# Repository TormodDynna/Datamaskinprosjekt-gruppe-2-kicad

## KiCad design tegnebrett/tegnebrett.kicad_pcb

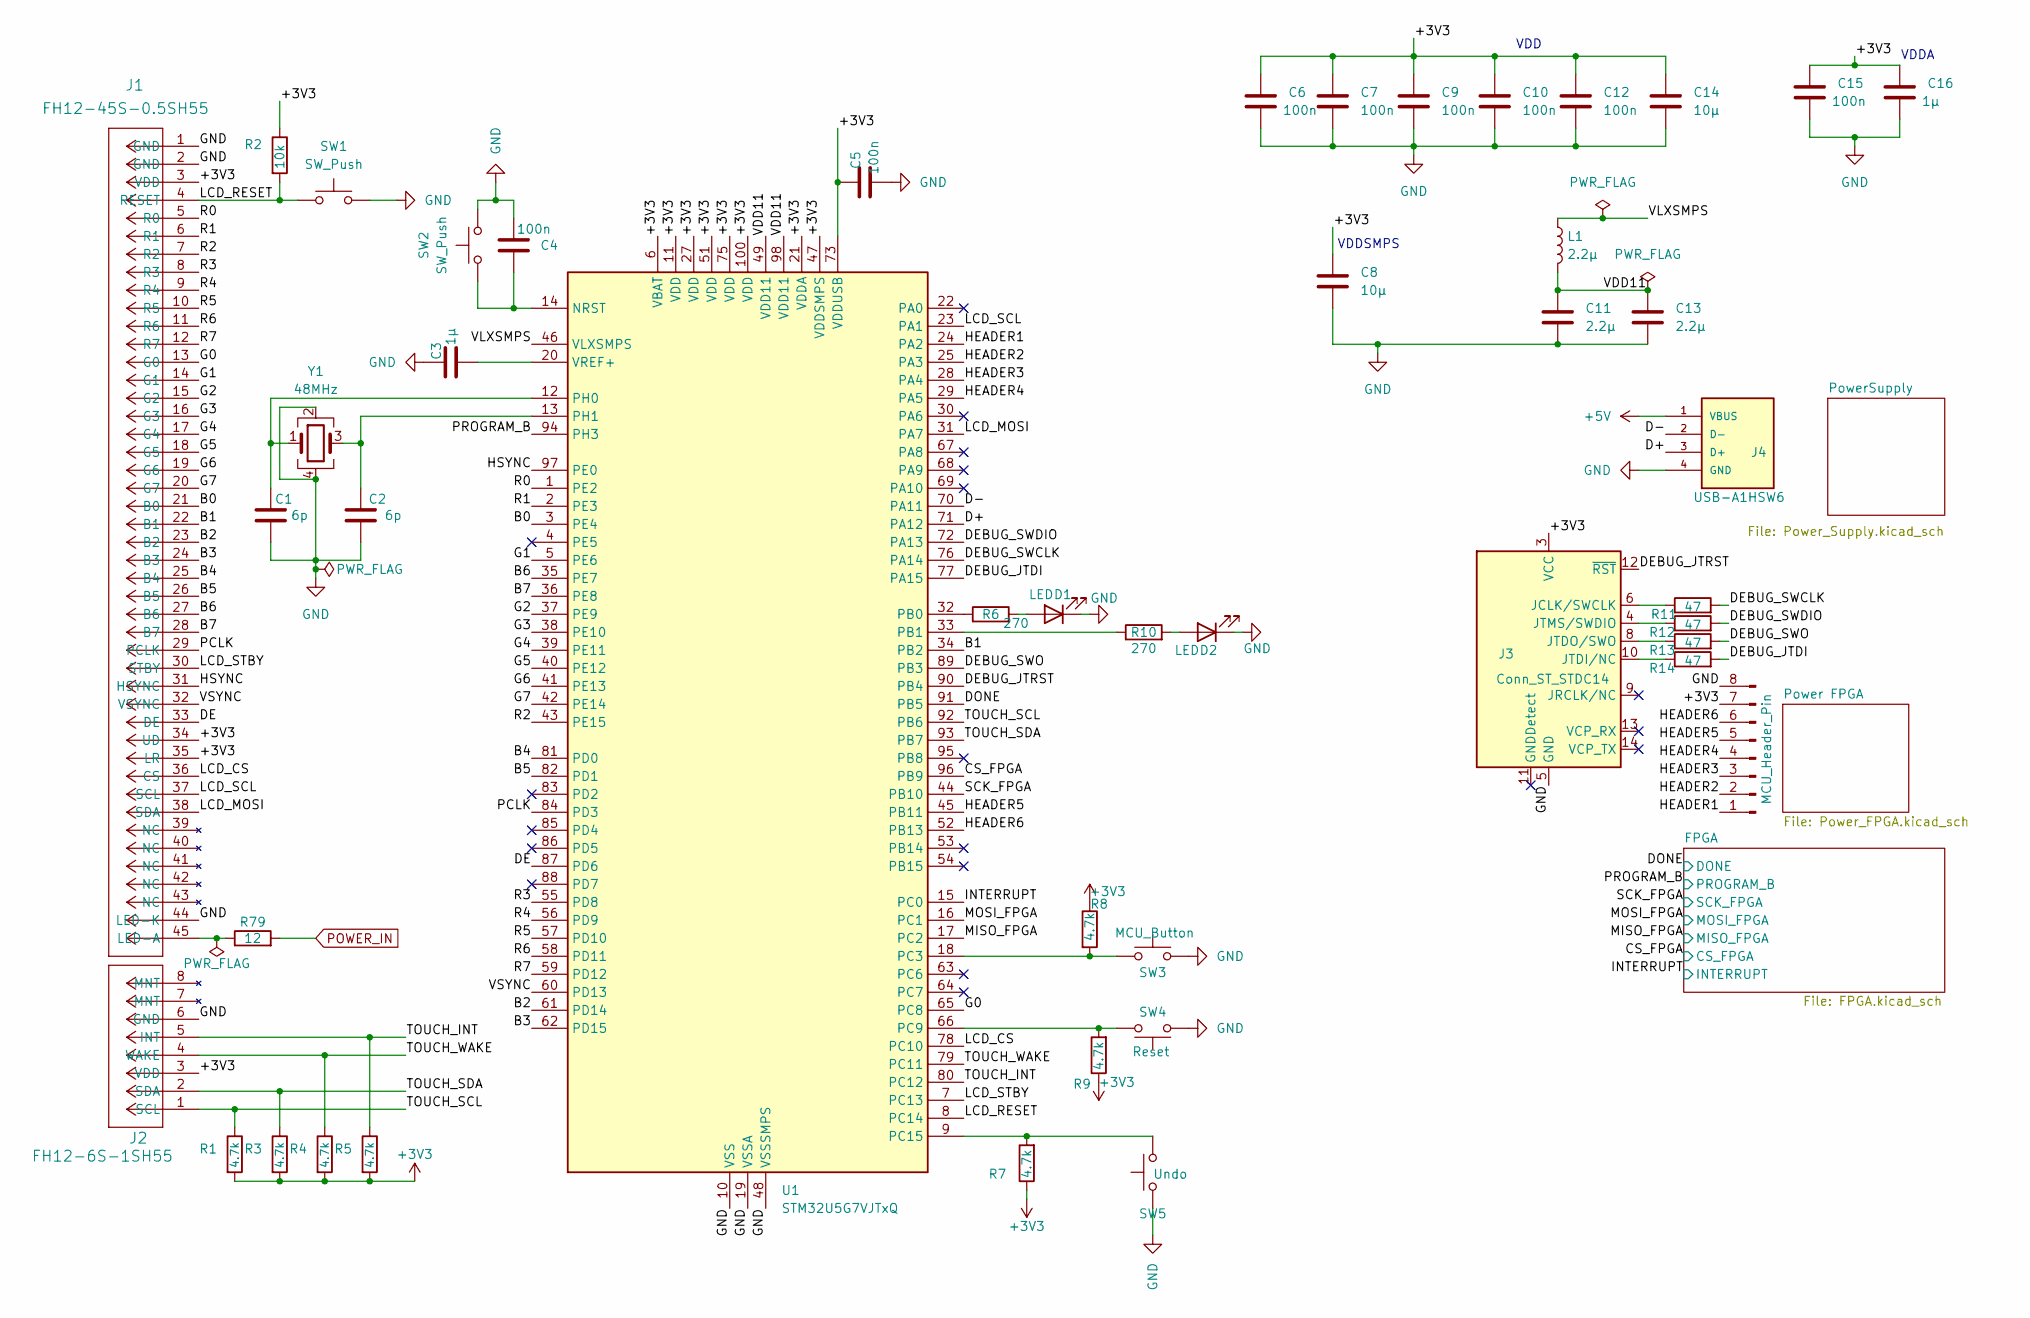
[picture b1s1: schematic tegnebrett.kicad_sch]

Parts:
C1, C2: 6p; C_0805_2012Metric_Pad1.18x1.45mm_HandSolder
C3, C16: 1µ; C_0805_2012Metric_Pad1.18x1.45mm_HandSolder
C4, C5, C6, C7, C9, C10, C12, C15: 100n; C_0805_2012Metric_Pad1.18x1.45mm_HandSolder
C8, C14: 10µ; C_1206_3216Metric_Pad1.33x1.80mm_HandSolder
C11, C13: 2.2µ; C_0805_2012Metric_Pad1.18x1.45mm_HandSolder
D1, D2: LED; LED_LTST-C193KGKT-5A_LTO-M
J1: FH12-45S-0.5SH55; CONN_45S-0.5SH55
J2: FH12-6S-1SH55; CON6_1X6_DRBF_HST_HIR
J3: Conn_ST_STDC14; PinHeader_2x07_P1.27mm_Vertical
J4: USB-A1HSW6; OST_USB-A1HSW6; PARTREV A
J5: MCU_Header_Pin; PinHeader_1x08_P2.54mm_Vertical
L1: 2.2µ; L_0805_2012Metric_Pad1.15x1.40mm_HandSolder
R1, R3, R4, R5, R7, R8, R9: 4.7k; R_0805_2012Metric_Pad1.20x1.40mm_HandSolder
R2: 10k; R_0805_2012Metric_Pad1.20x1.40mm_HandSolder
R6, R10: 270; R_0805_2012Metric_Pad1.20x1.40mm_HandSolder
R11, R12, R13, R14: 47; R_0805_2012Metric_Pad1.20x1.40mm_HandSolder
R79: 12; R_0805_2012Metric_Pad1.20x1.40mm_HandSolder
SW1, SW2: SW_Push; SW_PS1024ALRED
SW3: MCU_Button; SW_PS1024ALRED
SW4: Reset; SW_KS11R23CQD
SW5: Undo; SW_KS11R23CQD
U1: STM32U5G7VJTxQ; LQFP-100_14x14mm_P0.5mm
Y1: 48MHz; XRCGB48M000F4M00R0_MUR

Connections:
+3V3: C5.1, C6.1, C7.1, C8.1, C9.1, C10.1, C12.1, C14.1, C15.1, C16.1, J1.3 (VDD), J1.34 (UD), J1.35 (LR), J2.3 (VDD), J3.3 (VCC), J5.7, R1.2, R2.1, R3.2, R4.2, R5.2, R7.1, R8.1, R9.1, U1.6 (VBAT), U1.11 (VDD), U1.21 (VDDA), U1.27 (VDD), U1.47 (VDDSMPS), U1.51 (VDD), U1.73 (VDDUSB), U1.75 (VDD), U1.100 (VDD); also elsewhere on the board
+5V: J4.1 (VBUS); also elsewhere on the board
/B0: J1.21 (B0), U1.3 (PE4)
/B1: J1.22 (B1), U1.34 (PB2)
/B2: J1.23 (B2), U1.61 (PD14)
/B3: J1.24 (B3), U1.62 (PD15)
/B4: J1.25 (B4), U1.81 (PD0)
/B5: J1.26 (B5), U1.82 (PD1)
/B6: J1.27 (B6), U1.35 (PE7)
/B7: J1.28 (B7), U1.36 (PE8)
/CS_FPGA: U1.96 (PB9); also elsewhere on the board
/D+: J4.3 (D+), U1.71 (PA12)
/D-: J4.2 (D-), U1.70 (PA11)
/DE: J1.33 (DE), U1.87 (PD6)
/DEBUG_JTDI: R14.2, U1.77 (PA15)
/DEBUG_JTRST: J3.12 (~RST), U1.90 (PB4)
/DEBUG_SWCLK: R11.2, U1.76 (PA14)
/DEBUG_SWDIO: R12.2, U1.72 (PA13)
/DEBUG_SWO: R13.2, U1.89 (PB3)
/DONE: U1.91 (PB5); also elsewhere on the board
/G0: J1.13 (G0), U1.65 (PC8)
/G1: J1.14 (G1), U1.5 (PE6)
/G2: J1.15 (G2), U1.37 (PE9)
/G3: J1.16 (G3), U1.38 (PE10)
/G4: J1.17 (G4), U1.39 (PE11)
/G5: J1.18 (G5), U1.40 (PE12)
/G6: J1.19 (G6), U1.41 (PE13)
/G7: J1.20 (G7), U1.42 (PE14)
/HEADER1: J5.1, U1.24 (PA2)
/HEADER2: J5.2, U1.25 (PA3)
/HEADER3: J5.3, U1.28 (PA4)
/HEADER4: J5.4, U1.29 (PA5)
/HEADER5: J5.5, U1.45 (PB11)
/HEADER6: J5.6, U1.52 (PB13)
/HSYNC: J1.31 (HSYNC), U1.97 (PE0)
/INTERRUPT: U1.15 (PC0); also elsewhere on the board
/LCD_CS: J1.36 (CS), U1.78 (PC10)
/LCD_MOSI: J1.38 (SDA), U1.31 (PA7)
/LCD_RESET: J1.4 (RESET), R2.2, SW1.1, U1.8 (PC14)
/LCD_SCL: J1.37 (SCL), U1.23 (PA1)
/LCD_STBY: J1.30 (STBY), U1.7 (PC13)
/MISO_FPGA: U1.17 (PC2); also elsewhere on the board
/MOSI_FPGA: U1.16 (PC1); also elsewhere on the board
/PCLK: J1.29 (PCLK), U1.84 (PD3)
/PROGRAM_B: U1.94 (PH3); also elsewhere on the board
/R0: J1.5 (R0), U1.1 (PE2)
/R1: J1.6 (R1), U1.2 (PE3)
/R2: J1.7 (R2), U1.43 (PE15)
/R3: J1.8 (R3), U1.55 (PD8)
/R4: J1.9 (R4), U1.56 (PD9)
/R5: J1.10 (R5), U1.57 (PD10)
/R6: J1.11 (R6), U1.58 (PD11)
/R7: J1.12 (R7), U1.59 (PD12)
/SCK_FPGA: U1.44 (PB10); also elsewhere on the board
/TOUCH_INT: J2.5 (INT), R5.1, U1.80 (PC12)
/TOUCH_SCL: J2.1 (SCL), R1.1, U1.92 (PB6)
/TOUCH_SDA: J2.2 (SDA), R3.1, U1.93 (PB7)
/TOUCH_WAKE: J2.4 (WAKE), R4.1, U1.79 (PC11)
/VDD11: C11.1, C13.1, L1.2, U1.49 (VDD11), U1.98 (VDD11)
/VLXSMPS: L1.1, U1.46 (VLXSMPS)
/VSYNC: J1.32 (VSYNC), U1.60 (PD13)
GND: C1.2, C2.2, C3.1, C4.2, C5.2, C6.2, C7.2, C8.2, C9.2, C10.2, C11.2, C12.2, C13.2, C14.2, C15.2, C16.2, D1.1 (K), D2.1 (K), J1.1 (GND), J1.2 (GND), J1.44 (LED-K), J2.6 (GND), J3.5 (GND), J3.7 (GND), J4.4 (GND), J5.8, SW1.2, SW2.2, SW3.2, SW4.1, SW5.1, U1.10 (VSS), U1.19 (VSSA), U1.26 (VSS), U1.48 (VSSSMPS), U1.50 (VSS), U1.74 (VSS), U1.99 (VSS), Y1.2, Y1.4; also elsewhere on the board
unnamed: D1.2 (A), R6.2
unnamed: D2.2 (A), R10.2
unnamed: J1.45 (LED-A), R79.1
unnamed: J3.6 (JCLK/SWCLK), R11.1
unnamed: J3.10 (JTDI/NC), R14.1
unnamed: J3.8 (JTDO/SWO), R13.1
unnamed: J3.4 (JTMS/SWDIO), R12.1
unnamed: C4.1, SW2.1, U1.14 (NRST)
unnamed: R6.1, U1.32 (PB0)
unnamed: R10.1, U1.33 (PB1)
unnamed: R8.2, SW3.1, U1.18 (PC3)
unnamed: R9.2, SW4.3, U1.66 (PC9)
unnamed: R7.2, SW5.3, U1.9 (PC15)
unnamed: C1.1, U1.12 (PH0), Y1.1
unnamed: C2.1, U1.13 (PH1), Y1.3
unnamed: C3.2, U1.20 (VREF+)
POWER_IN: R79.2; also elsewhere on the board

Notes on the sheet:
VDD
VDDSMPS
VDDA

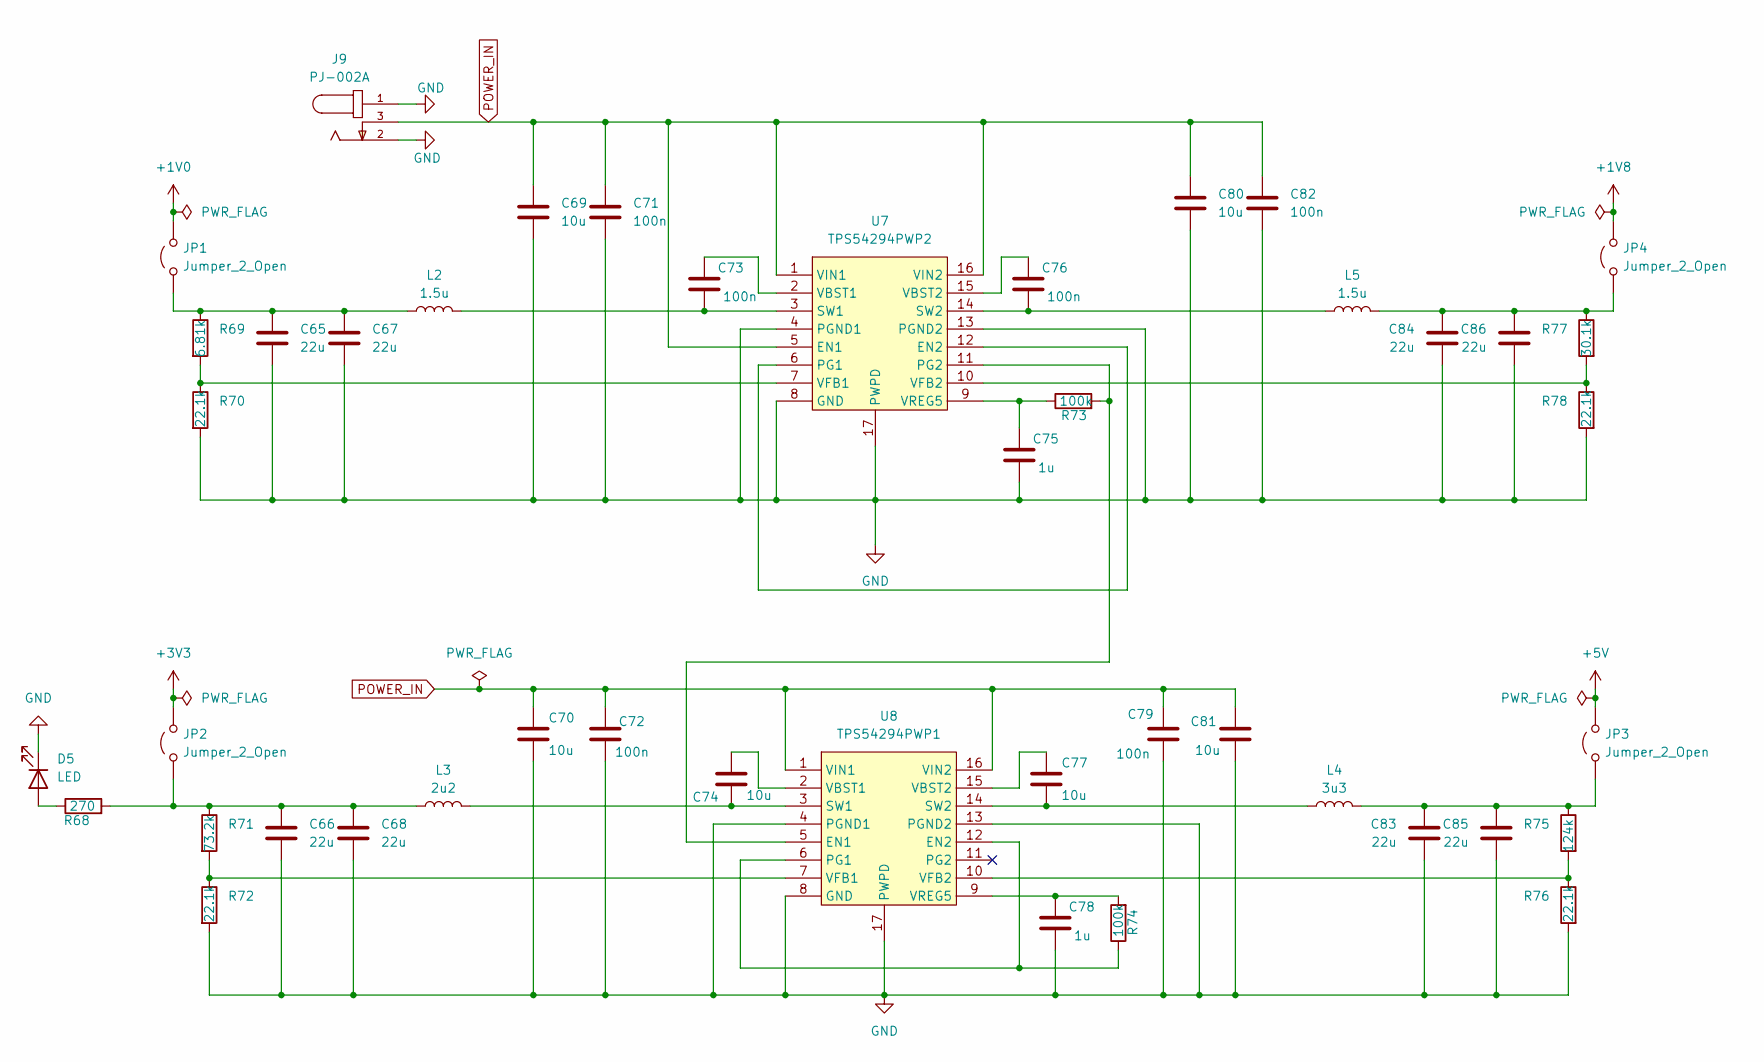
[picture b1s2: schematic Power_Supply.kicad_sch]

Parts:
C65, C66, C67, C68, C83, C84, C85, C86: 22u; C_1206_3216Metric_Pad1.33x1.80mm_HandSolder
C69, C70, C74, C77, C80, C81: 10u; C_1206_3216Metric_Pad1.33x1.80mm_HandSolder
C71, C72, C73, C76, C79, C82: 100n; C_0805_2012Metric_Pad1.18x1.45mm_HandSolder
C75, C78: 1u; C_0805_2012Metric_Pad1.18x1.45mm_HandSolder
D5: LED; LED_LTST-C193KGKT-5A_LTO-M
J9: PJ-002A; CUI_PJ-002A
JP1, JP2, JP3, JP4: Jumper_2_Open; PinHeader_1x02_P2.54mm_Vertical
L2, L5: 1.5u; L_0805_2012Metric_Pad1.15x1.40mm_HandSolder
L3: 2u2; L_0805_2012Metric_Pad1.15x1.40mm_HandSolder
L4: 3u3; L_0805_2012Metric_Pad1.15x1.40mm_HandSolder
R68: 270; R_0805_2012Metric_Pad1.20x1.40mm_HandSolder
R69: 6.81k; R_0805_2012Metric_Pad1.20x1.40mm_HandSolder
R70, R72, R76, R78: 22.1k; R_0805_2012Metric_Pad1.20x1.40mm_HandSolder
R71: 73.2k; R_0805_2012Metric_Pad1.20x1.40mm_HandSolder
R73, R74: 100k; R_0805_2012Metric_Pad1.20x1.40mm_HandSolder
R75: 124k; R_0805_2012Metric_Pad1.20x1.40mm_HandSolder
R77: 30.1k; R_0805_2012Metric_Pad1.20x1.40mm_HandSolder
U7: TPS54294PWP2; PWP16_2P31X2P46
U8: TPS54294PWP1; PWP16_2P31X2P46

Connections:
+1V0: JP1.2 (B); also elsewhere on the board
+1V8: JP4.2 (B); also elsewhere on the board
+3V3: JP2.2 (B); also elsewhere on the board
+5V: JP3.2 (B); also elsewhere on the board
GND: C65.2, C66.2, C67.2, C68.2, C69.2, C70.2, C71.2, C72.2, C75.2, C78.2, C79.2, C80.2, C81.2, C82.2, C83.2, C84.2, C85.2, C86.2, D5.1 (K), J9.1, J9.2, R70.2, R72.2, R76.2, R78.2, U7.4 (PGND1), U7.8 (GND), U7.13 (PGND2), U7.17 (PWPD), U8.4 (PGND1), U8.8 (GND), U8.13 (PGND2), U8.17 (PWPD); also elsewhere on the board
unnamed: D5.2 (A), R68.1
unnamed: C65.1, C67.1, JP1.1 (A), L2.1, R69.1
unnamed: C66.1, C68.1, JP2.1 (A), L3.1, R68.2, R71.1
unnamed: C83.1, C85.1, JP3.1 (A), L4.1, R75.1
unnamed: C84.1, C86.1, JP4.1 (A), L5.1, R77.1
unnamed: U7.6 (PG1), U7.12 (EN2)
unnamed: R73.2, U7.11 (PG2), U8.5 (EN1)
unnamed: C73.2, L2.2, U7.3 (SW1)
unnamed: C76.2, L5.2, U7.14 (SW2)
unnamed: C73.1, U7.2 (VBST1)
unnamed: C76.1, U7.15 (VBST2)
unnamed: R69.2, R70.1, U7.7 (VFB1)
unnamed: R77.2, R78.1, U7.10 (VFB2)
unnamed: C75.1, R73.1, U7.9 (VREG5)
unnamed: R74.1, U8.6 (PG1), U8.12 (EN2)
unnamed: C74.2, L3.2, U8.3 (SW1)
unnamed: C77.2, L4.2, U8.14 (SW2)
unnamed: C74.1, U8.2 (VBST1)
unnamed: C77.1, U8.15 (VBST2)
unnamed: R71.2, R72.1, U8.7 (VFB1)
unnamed: R75.2, R76.1, U8.10 (VFB2)
unnamed: C78.1, R74.2, U8.9 (VREG5)
POWER_IN: C69.1, C70.1, C71.1, C72.1, C79.1, C80.1, C81.1, C82.1, J9.3, U7.1 (VIN1), U7.5 (EN1), U7.16 (VIN2), U8.1 (VIN1), U8.16 (VIN2); also elsewhere on the board

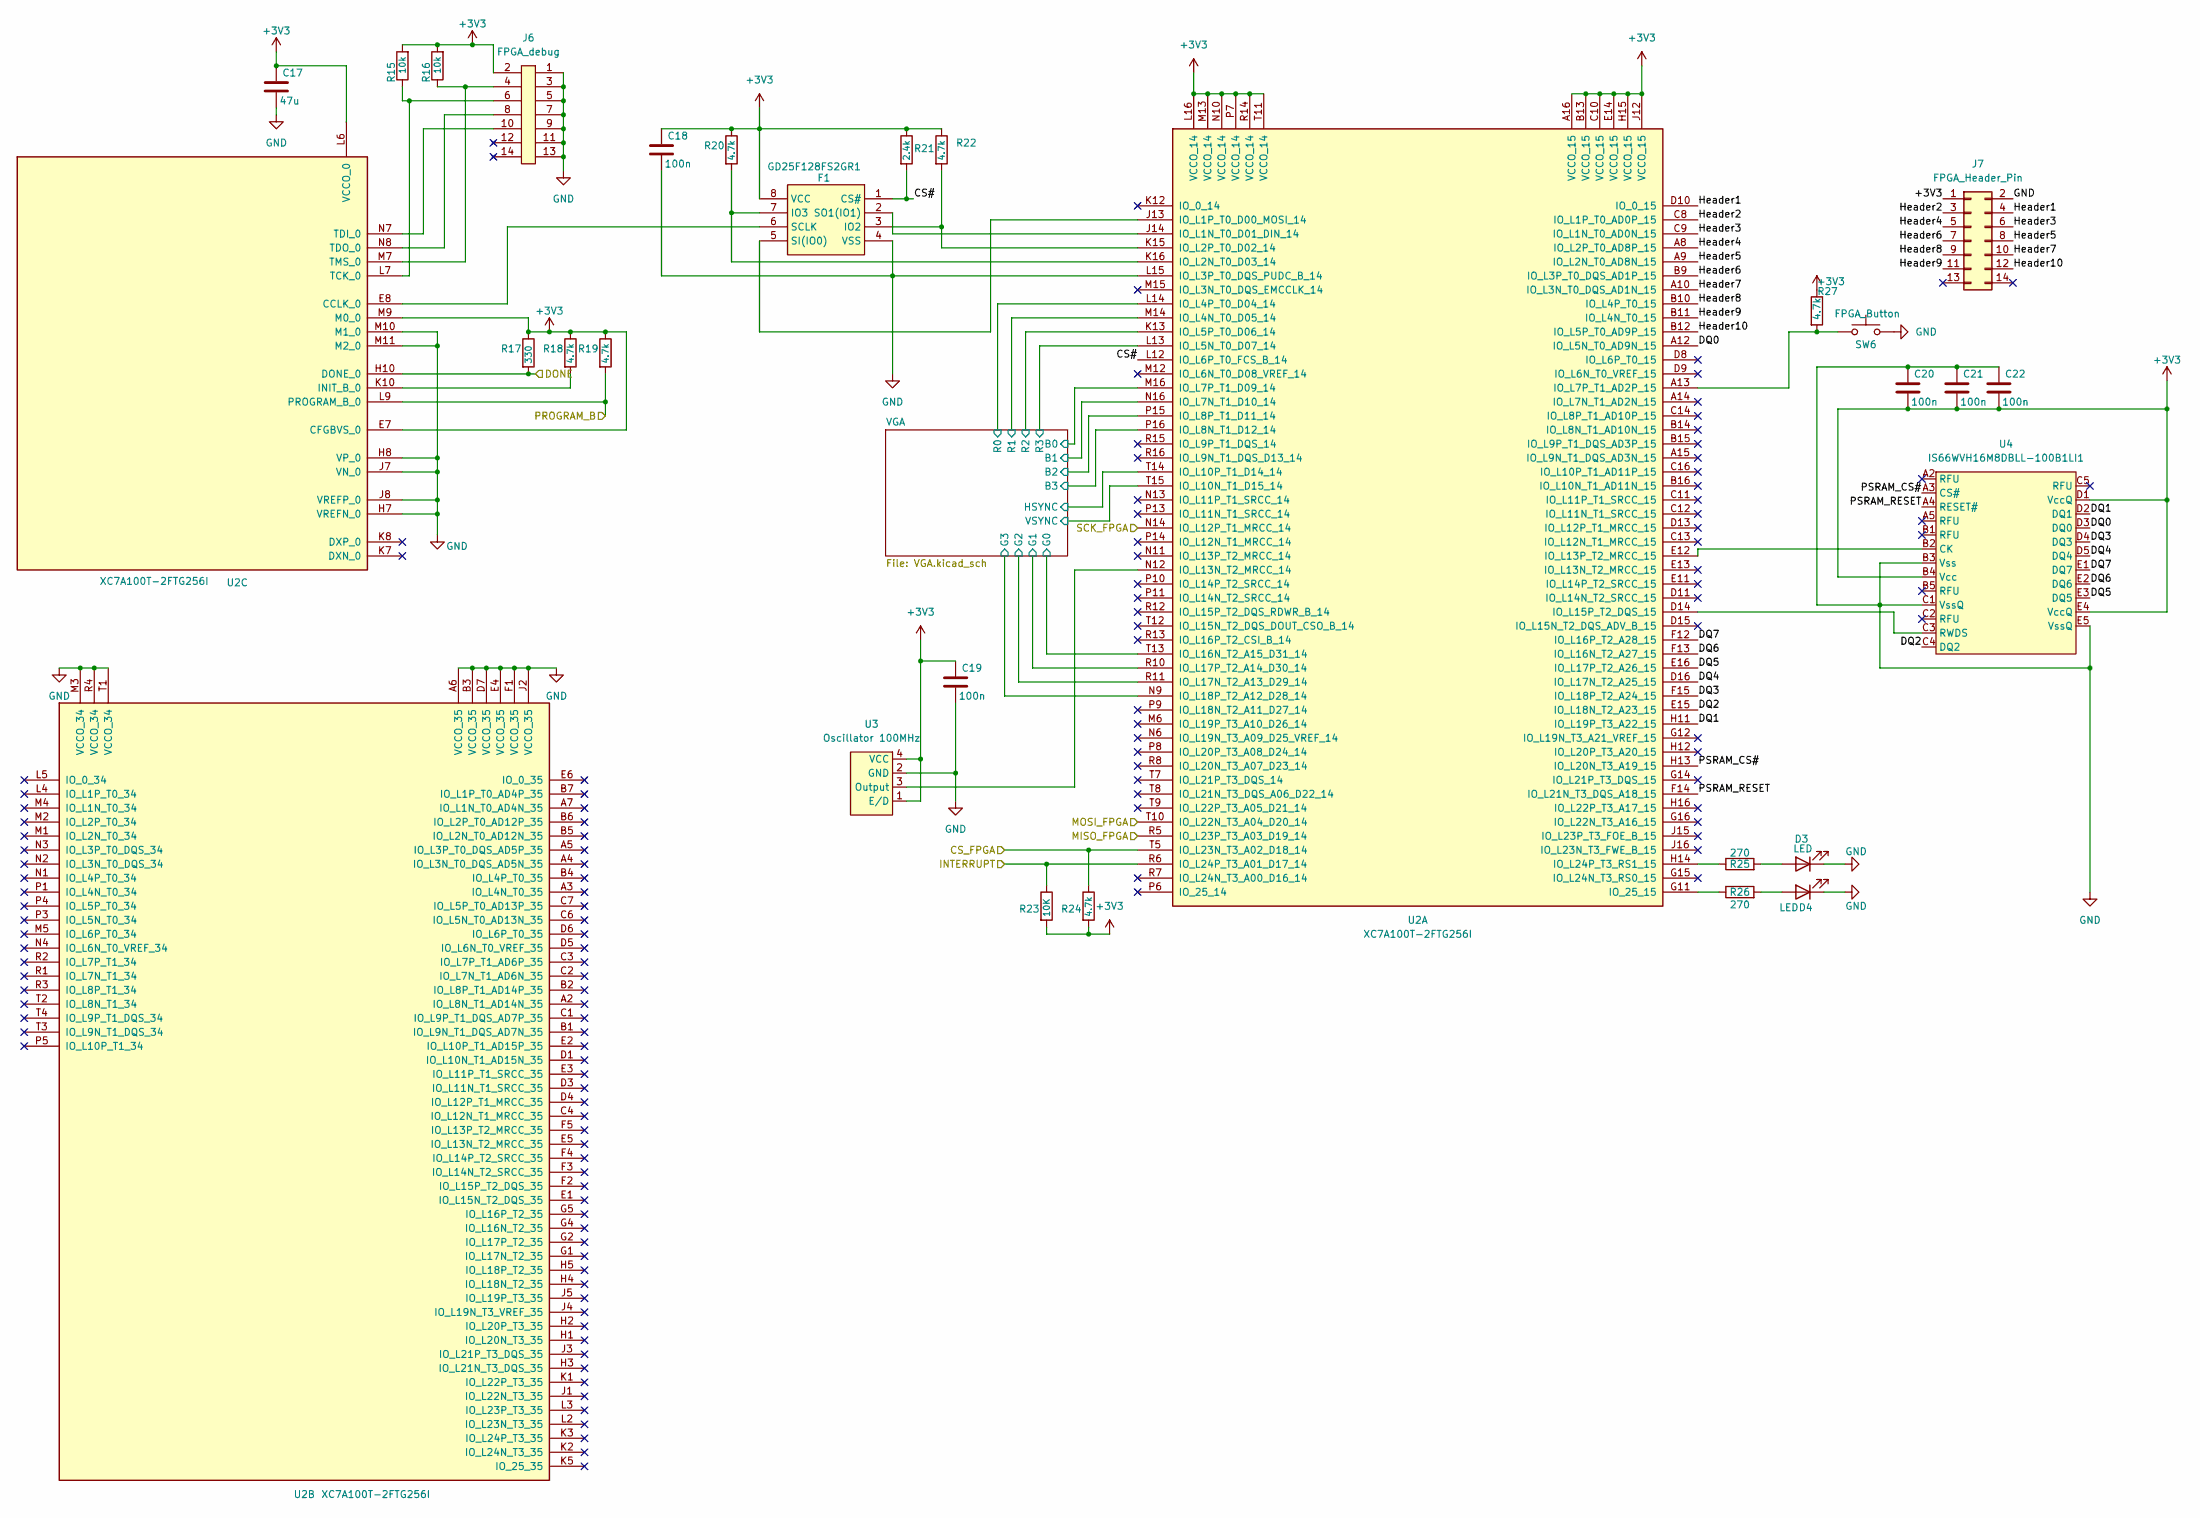
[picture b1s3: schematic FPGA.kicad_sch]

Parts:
C17: 47u; C_0805_2012Metric_Pad1.18x1.45mm_HandSolder
C18, C19, C20, C21, C22: 100n; C_0805_2012Metric_Pad1.18x1.45mm_HandSolder
D3, D4: LED; LED_LTST-C193KGKT-5A_LTO-M
F1: GD25F128FS2GR1; flash_tegnebrett
J6: FPGA_debug; PinHeader_2x07_P2.54mm_Vertical
J7: FPGA_Header_Pin; PinHeader_2x07_P2.54mm_Vertical
R15, R16: 10k; R_0805_2012Metric_Pad1.20x1.40mm_HandSolder
R17: 330; R_0805_2012Metric_Pad1.20x1.40mm_HandSolder
R18, R19, R20, R22, R24, R27: 4.7k; R_0805_2012Metric_Pad1.20x1.40mm_HandSolder
R21: 2.4k; R_0805_2012Metric_Pad1.20x1.40mm_HandSolder
R23: 10K; R_0805_2012Metric_Pad1.20x1.40mm_HandSolder
R25, R26: 270; R_0805_2012Metric_Pad1.20x1.40mm_HandSolder
SW6: FPGA_Button; SW_PS1024ALRED
U2: XC7A100T-2FTG256I; fpga
U3: Oscillator 100MHz; CWX813-100.0M_CNW
U4: IS66WVH16M8DBLL-100B1LI1; psram

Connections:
+3V3: C17.1, C18.1, C19.1, C20.2, C21.2, C22.2, F1.8 (VCC), J6.2, J7.1, R15.2, R16.2, R17.1, R18.1, R19.1, R20.1, R21.1, R22.1, R23.2, R24.2, R27.1, U2.A16 (VCCO_15), U2.B13 (VCCO_15), U2.C10 (VCCO_15), U2.E7 (CFGBVS_0), U2.E14 (VCCO_15), U2.H15 (VCCO_15), U2.J12 (VCCO_15), U2.L6 (VCCO_0), U2.L16 (VCCO_14), U2.M9 (M0_0), U2.M13 (VCCO_14), U2.N10 (VCCO_14), U2.P7 (VCCO_14), U2.R14 (VCCO_14), U2.T11 (VCCO_14), U3.1 (E/D), U3.4 (VCC), U4.B4 (Vcc), U4.D1 (VccQ), U4.E4 (VccQ); also elsewhere on the board
/CS_FPGA: R24.1, U2.T5 (IO_L23N_T3_A02_D18_14); also elsewhere on the board
/DONE: R17.2, U2.H10 (DONE_0); also elsewhere on the board
/FPGA/CS#: F1.1 (CS#), R21.2, U2.L12 (IO_L6P_T0_FCS_B_14)
/FPGA/DQ0: U2.A12 (IO_L5N_T0_AD9N_15), U4.D3 (DQ0)
/FPGA/DQ1: U2.H11 (IO_L19P_T3_A22_15), U4.D2 (DQ1)
/FPGA/DQ2: U2.E15 (IO_L18N_T2_A23_15), U4.C4 (DQ2)
/FPGA/DQ3: U2.F15 (IO_L18P_T2_A24_15), U4.D4 (DQ3)
/FPGA/DQ4: U2.D16 (IO_L17N_T2_A25_15), U4.D5 (DQ4)
/FPGA/DQ5: U2.E16 (IO_L17P_T2_A26_15), U4.E3 (DQ5)
/FPGA/DQ6: U2.F13 (IO_L16N_T2_A27_15), U4.E2 (DQ6)
/FPGA/DQ7: U2.F12 (IO_L16P_T2_A28_15), U4.E1 (DQ7)
/FPGA/Header1: J7.4, U2.D10 (IO_0_15)
/FPGA/Header2: J7.3, U2.C8 (IO_L1P_T0_AD0P_15)
/FPGA/Header3: J7.6, U2.C9 (IO_L1N_T0_AD0N_15)
/FPGA/Header4: J7.5, U2.A8 (IO_L2P_T0_AD8P_15)
/FPGA/Header5: J7.8, U2.A9 (IO_L2N_T0_AD8N_15)
/FPGA/Header6: J7.7, U2.B9 (IO_L3P_T0_DQS_AD1P_15)
/FPGA/Header7: J7.10, U2.A10 (IO_L3N_T0_DQS_AD1N_15)
/FPGA/Header8: J7.9, U2.B10 (IO_L4P_T0_15)
/FPGA/Header9: J7.11, U2.B11 (IO_L4N_T0_15)
/FPGA/Header10: J7.12, U2.B12 (IO_L5P_T0_AD9P_15)
/FPGA/PSRAM_CS#: U2.H13 (IO_L20N_T3_A19_15), U4.A3 (CS#)
/FPGA/PSRAM_RESET: U2.F14 (IO_L21N_T3_DQS_A18_15), U4.A4 (RESET#)
/FPGA/VGA/B0: U2.M16 (IO_L7P_T1_D09_14); also elsewhere on the board
/FPGA/VGA/B1: U2.N16 (IO_L7N_T1_D10_14); also elsewhere on the board
/FPGA/VGA/B2: U2.P15 (IO_L8P_T1_D11_14); also elsewhere on the board
/FPGA/VGA/B3: U2.P16 (IO_L8N_T1_D12_14); also elsewhere on the board
/FPGA/VGA/G0: U2.T13 (IO_L16N_T2_A15_D31_14); also elsewhere on the board
/FPGA/VGA/G1: U2.R10 (IO_L17P_T2_A14_D30_14); also elsewhere on the board
/FPGA/VGA/G2: U2.R11 (IO_L17N_T2_A13_D29_14); also elsewhere on the board
/FPGA/VGA/G3: U2.N9 (IO_L18P_T2_A12_D28_14); also elsewhere on the board
/FPGA/VGA/HSYNC: U2.T14 (IO_L10P_T1_D14_14); also elsewhere on the board
/FPGA/VGA/R0: U2.L14 (IO_L4P_T0_D04_14); also elsewhere on the board
/FPGA/VGA/R1: U2.M14 (IO_L4N_T0_D05_14); also elsewhere on the board
/FPGA/VGA/R2: U2.K13 (IO_L5P_T0_D06_14); also elsewhere on the board
/FPGA/VGA/R3: U2.L13 (IO_L5N_T0_D07_14); also elsewhere on the board
/FPGA/VGA/VSYNC: U2.T15 (IO_L10N_T1_D15_14); also elsewhere on the board
/INTERRUPT: R23.1, U2.R6 (IO_L24P_T3_A01_D17_14); also elsewhere on the board
/MISO_FPGA: U2.R5 (IO_L23P_T3_A03_D19_14); also elsewhere on the board
/MOSI_FPGA: U2.T10 (IO_L22N_T3_A04_D20_14); also elsewhere on the board
/PROGRAM_B: R19.2, U2.L9 (PROGRAM_B_0); also elsewhere on the board
/SCK_FPGA: U2.N14 (IO_L12P_T1_MRCC_14); also elsewhere on the board
GND: C17.2, C18.2, C19.2, C20.1, C21.1, C22.1, D3.1 (K), D4.1 (K), F1.4 (VSS), J6.1, J6.3, J6.5, J6.7, J6.9, J6.11, J6.13, J7.2, SW6.2, U2.A6 (VCCO_35), U2.B3 (VCCO_35), U2.D7 (VCCO_35), U2.E4 (VCCO_35), U2.F1 (VCCO_35), U2.H7 (VREFN_0), U2.H8 (VP_0), U2.J2 (VCCO_35), U2.J7 (VN_0), U2.J8 (VREFP_0), U2.L15 (IO_L3P_T0_DQS_PUDC_B_14), U2.M3 (VCCO_34), U2.M10 (M1_0), U2.M11 (M2_0), U2.R4 (VCCO_34), U2.T1 (VCCO_34), U3.2 (GND), U4.B3 (Vss), U4.C1 (VssQ), U4.E5 (VssQ); also elsewhere on the board
unnamed: D3.2 (A), R25.2
unnamed: D4.2 (A), R26.2
unnamed: F1.3 (IO2), R22.2, U2.K15 (IO_L2P_T0_D02_14)
unnamed: F1.7 (IO3), R20.2, U2.K16 (IO_L2N_T0_D03_14)
unnamed: F1.6 (SCLK), U2.E8 (CCLK_0)
unnamed: F1.5 (SI(IO0)), U2.J13 (IO_L1P_T0_D00_MOSI_14)
unnamed: F1.2 (SO1(IO1)), U2.J14 (IO_L1N_T0_D01_DIN_14)
unnamed: R26.1, U2.G11 (IO_25_15)
unnamed: R27.2, SW6.1, U2.A13 (IO_L7P_T1_AD2P_15)
unnamed: U2.N12 (IO_L13N_T2_MRCC_14), U3.3 (Output)
unnamed: U2.E12 (IO_L13P_T2_MRCC_15), U4.B2 (CK)
unnamed: U2.D14 (IO_L15P_T2_DQS_15), U4.C3 (RWDS)
unnamed: R25.1, U2.H14 (IO_L24P_T3_RS1_15)
unnamed: R18.2, U2.K10 (INIT_B_0)
unnamed: J6.6, R15.1, U2.L7 (TCK_0)
unnamed: J6.10, U2.N7 (TDI_0)
unnamed: J6.8, U2.N8 (TDO_0)
unnamed: J6.4, R16.1, U2.M7 (TMS_0)

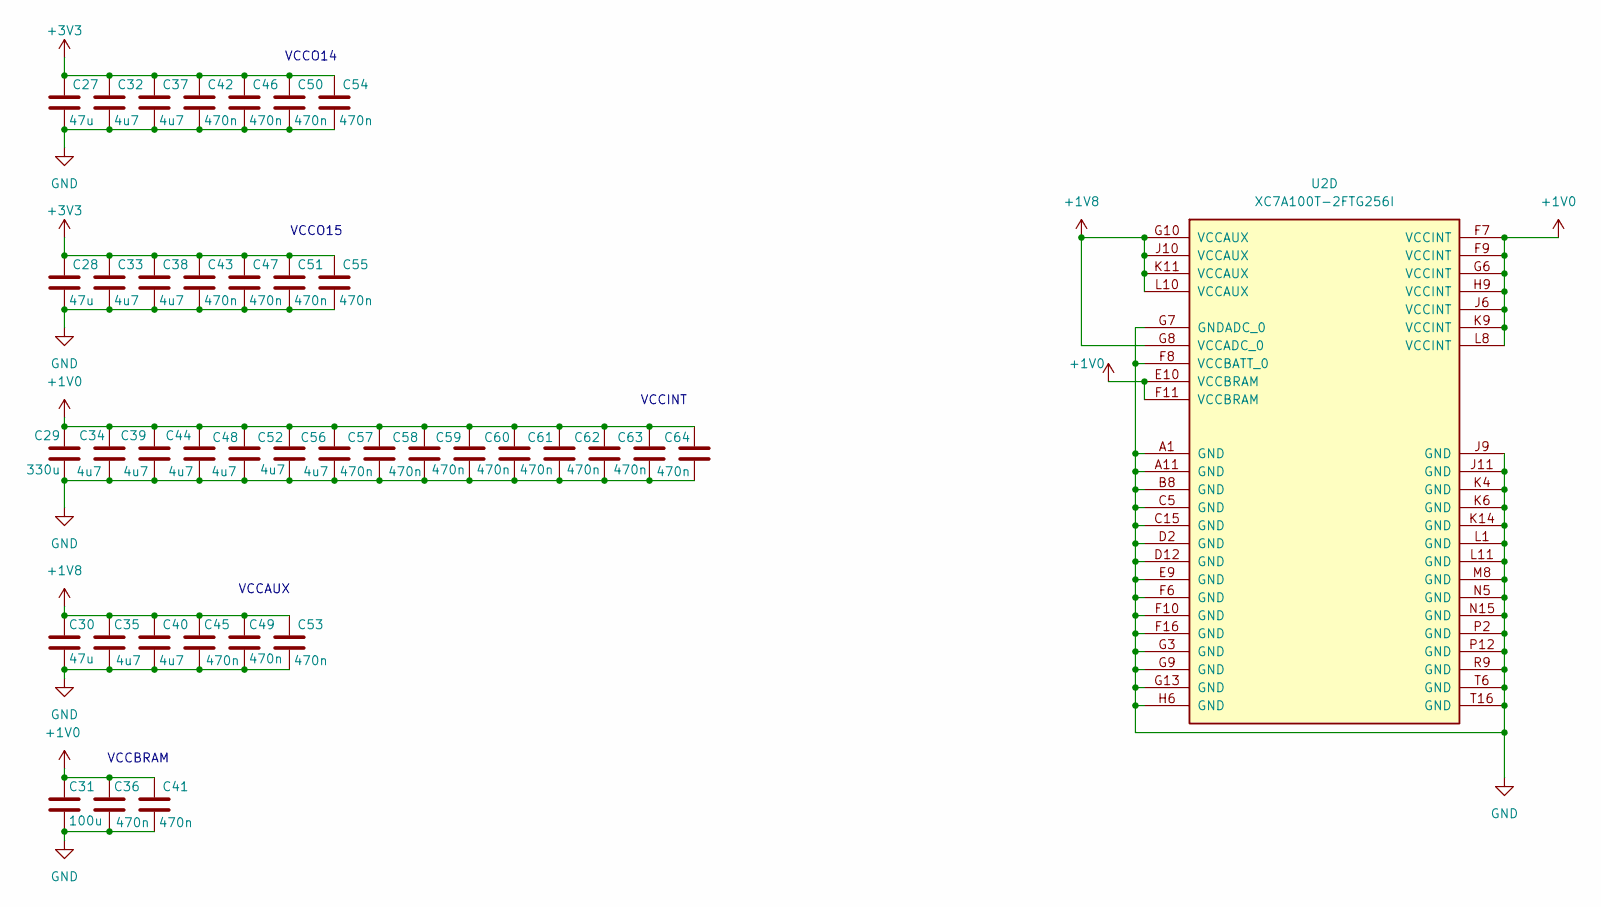
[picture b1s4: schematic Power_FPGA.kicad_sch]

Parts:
C27, C28, C30: 47u; C_0805_2012Metric_Pad1.18x1.45mm_HandSolder
C29: 330u; C_1210_3225Metric_Pad1.33x2.70mm_HandSolder
C31: 100u; C_1206_3216Metric_Pad1.33x1.80mm_HandSolder
C32, C33, C34, C35, C37, C38, C39, C40, C44, C48, C52, C56: 4u7; C_0805_2012Metric_Pad1.18x1.45mm_HandSolder
C36, C41, C42, C43, C45, C46, C47, C49, C50, C51, C53, C54, C55, C57, C58, C59, C60, C61, C62, C63, C64: 470n; C_0805_2012Metric_Pad1.18x1.45mm_HandSolder
U2: XC7A100T-2FTG256I; fpga

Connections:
+1V0: C29.1, C31.1, C34.1, C36.1, C39.1, C41.1, C44.1, C48.1, C52.1, C56.1, C57.1, C58.1, C59.1, C60.1, C61.1, C62.1, C63.1, C64.1, U2.E10 (VCCBRAM), U2.F7 (VCCINT), U2.F9 (VCCINT), U2.F11 (VCCBRAM), U2.G6 (VCCINT), U2.H9 (VCCINT), U2.J6 (VCCINT), U2.K9 (VCCINT), U2.L8 (VCCINT); also elsewhere on the board
+1V8: C30.1, C35.1, C40.1, C45.1, C49.1, C53.1, U2.G8 (VCCADC_0), U2.G10 (VCCAUX), U2.J10 (VCCAUX), U2.K11 (VCCAUX), U2.L10 (VCCAUX); also elsewhere on the board
+3V3: C27.1, C28.1, C32.1, C33.1, C37.1, C38.1, C42.1, C43.1, C46.1, C47.1, C50.1, C51.1, C54.1, C55.1; also elsewhere on the board
GND: C27.2, C28.2, C29.2, C30.2, C31.2, C32.2, C33.2, C34.2, C35.2, C36.2, C37.2, C38.2, C39.2, C40.2, C41.2, C42.2, C43.2, C44.2, C45.2, C46.2, C47.2, C48.2, C49.2, C50.2, C51.2, C52.2, C53.2, C54.2, C55.2, C56.2, C57.2, C58.2, C59.2, C60.2, C61.2, C62.2, C63.2, C64.2, U2.A1 (GND), U2.A11 (GND), U2.B8 (GND), U2.C5 (GND), U2.C15 (GND), U2.D2 (GND), U2.D12 (GND), U2.E9 (GND), U2.F6 (GND), U2.F8 (VCCBATT_0), U2.F10 (GND), U2.F16 (GND), U2.G3 (GND), U2.G7 (GNDADC_0), U2.G9 (GND), U2.G13 (GND), U2.H6 (GND), U2.J9 (GND), U2.J11 (GND), U2.K4 (GND), U2.K6 (GND), U2.K14 (GND), U2.L1 (GND), U2.L11 (GND), U2.M8 (GND), U2.N5 (GND), U2.N15 (GND), U2.P2 (GND), U2.P12 (GND), U2.R9 (GND), U2.T6 (GND), U2.T16 (GND); also elsewhere on the board

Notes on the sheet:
VCCBRAM
VCCO15
VCCINT
VCCO14
VCCAUX

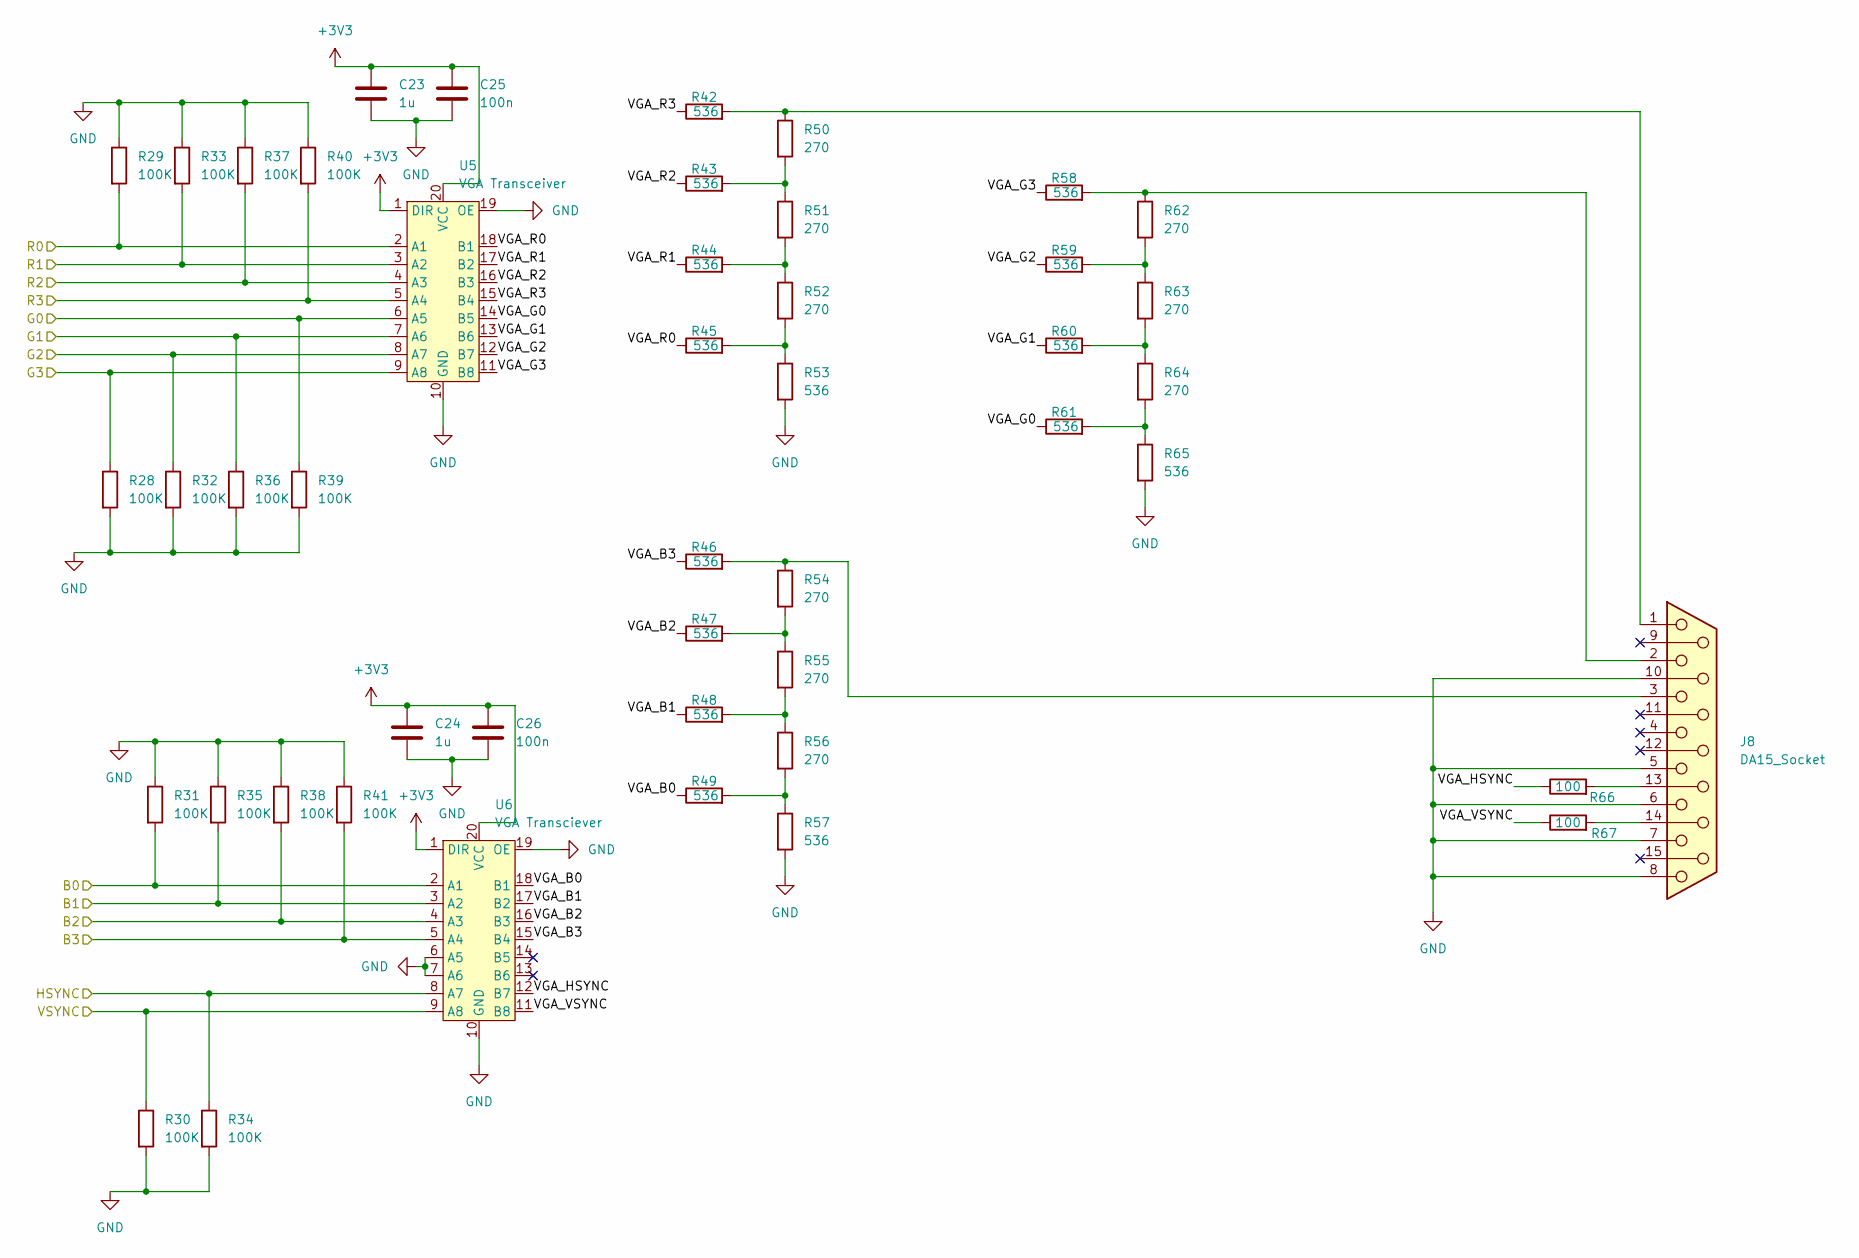
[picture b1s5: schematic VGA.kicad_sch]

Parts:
C23, C24: 1u; C_0805_2012Metric_Pad1.18x1.45mm_HandSolder
C25, C26: 100n; C_0805_2012Metric_Pad1.18x1.45mm_HandSolder
J8: DA15_Socket; AMPHENOL_L77HDE15SD1CH4RHNVGA
R28, R29, R30, R31, R32, R33, R34, R35, R36, R37, R38, R39, R40, R41: 100K; R_0805_2012Metric_Pad1.20x1.40mm_HandSolder
R42, R43, R44, R45, R46, R47, R48, R49, R53, R57, R58, R59, R60, R61, R65: 536; R_0805_2012Metric_Pad1.20x1.40mm_HandSolder
R50, R51, R52, R54, R55, R56, R62, R63, R64: 270; R_0805_2012Metric_Pad1.20x1.40mm_HandSolder
R66, R67: 100; R_0805_2012Metric_Pad1.20x1.40mm_HandSolder
U5: VGA Transceiver; SOP65P640X120-20N
U6: VGA Transciever; SOP65P640X120-20N

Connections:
+3V3: C23.1, C24.1, C25.1, C26.1, U5.1 (DIR), U5.20 (VCC), U6.1 (DIR), U6.20 (VCC); also elsewhere on the board
/FPGA/VGA/B0: R31.2, U6.2 (A1); also elsewhere on the board
/FPGA/VGA/B1: R35.2, U6.3 (A2); also elsewhere on the board
/FPGA/VGA/B2: R38.2, U6.4 (A3); also elsewhere on the board
/FPGA/VGA/B3: R41.2, U6.5 (A4); also elsewhere on the board
/FPGA/VGA/G0: R39.1, U5.6 (A5); also elsewhere on the board
/FPGA/VGA/G1: R36.1, U5.7 (A6); also elsewhere on the board
/FPGA/VGA/G2: R32.1, U5.8 (A7); also elsewhere on the board
/FPGA/VGA/G3: R28.1, U5.9 (A8); also elsewhere on the board
/FPGA/VGA/HSYNC: R34.1, U6.8 (A7); also elsewhere on the board
/FPGA/VGA/R0: R29.2, U5.2 (A1); also elsewhere on the board
/FPGA/VGA/R1: R33.2, U5.3 (A2); also elsewhere on the board
/FPGA/VGA/R2: R37.2, U5.4 (A3); also elsewhere on the board
/FPGA/VGA/R3: R40.2, U5.5 (A4); also elsewhere on the board
/FPGA/VGA/VGA_B0: R49.1, U6.18 (B1)
/FPGA/VGA/VGA_B1: R48.1, U6.17 (B2)
/FPGA/VGA/VGA_B2: R47.1, U6.16 (B3)
/FPGA/VGA/VGA_B3: R46.1, U6.15 (B4)
/FPGA/VGA/VGA_G0: R61.1, U5.14 (B5)
/FPGA/VGA/VGA_G1: R60.1, U5.13 (B6)
/FPGA/VGA/VGA_G2: R59.1, U5.12 (B7)
/FPGA/VGA/VGA_G3: R58.1, U5.11 (B8)
/FPGA/VGA/VGA_HSYNC: R66.1, U6.12 (B7)
/FPGA/VGA/VGA_R0: R45.1, U5.18 (B1)
/FPGA/VGA/VGA_R1: R44.1, U5.17 (B2)
/FPGA/VGA/VGA_R2: R43.1, U5.16 (B3)
/FPGA/VGA/VGA_R3: R42.1, U5.15 (B4)
/FPGA/VGA/VGA_VSYNC: R67.1, U6.11 (B8)
/FPGA/VGA/VSYNC: R30.1, U6.9 (A8); also elsewhere on the board
GND: C23.2, C24.2, C25.2, C26.2, J8.5, J8.6, J8.7, J8.8, J8.10, R28.2, R29.1, R30.2, R31.1, R32.2, R33.1, R34.2, R35.1, R36.2, R37.1, R38.1, R39.2, R40.1, R41.1, R53.2, R57.2, R65.2, U5.10 (GND), U5.19 (OE), U6.6 (A5), U6.7 (A6), U6.10 (GND), U6.19 (OE); also elsewhere on the board
unnamed: J8.13, R66.2
unnamed: J8.14, R67.2
unnamed: J8.1, R42.2, R50.1
unnamed: J8.2, R58.2, R62.1
unnamed: J8.3, R46.2, R54.1
unnamed: R43.2, R50.2, R51.1
unnamed: R44.2, R51.2, R52.1
unnamed: R45.2, R52.2, R53.1
unnamed: R47.2, R54.2, R55.1
unnamed: R48.2, R55.2, R56.1
unnamed: R49.2, R56.2, R57.1
unnamed: R59.2, R62.2, R63.1
unnamed: R60.2, R63.2, R64.1
unnamed: R61.2, R64.2, R65.1
